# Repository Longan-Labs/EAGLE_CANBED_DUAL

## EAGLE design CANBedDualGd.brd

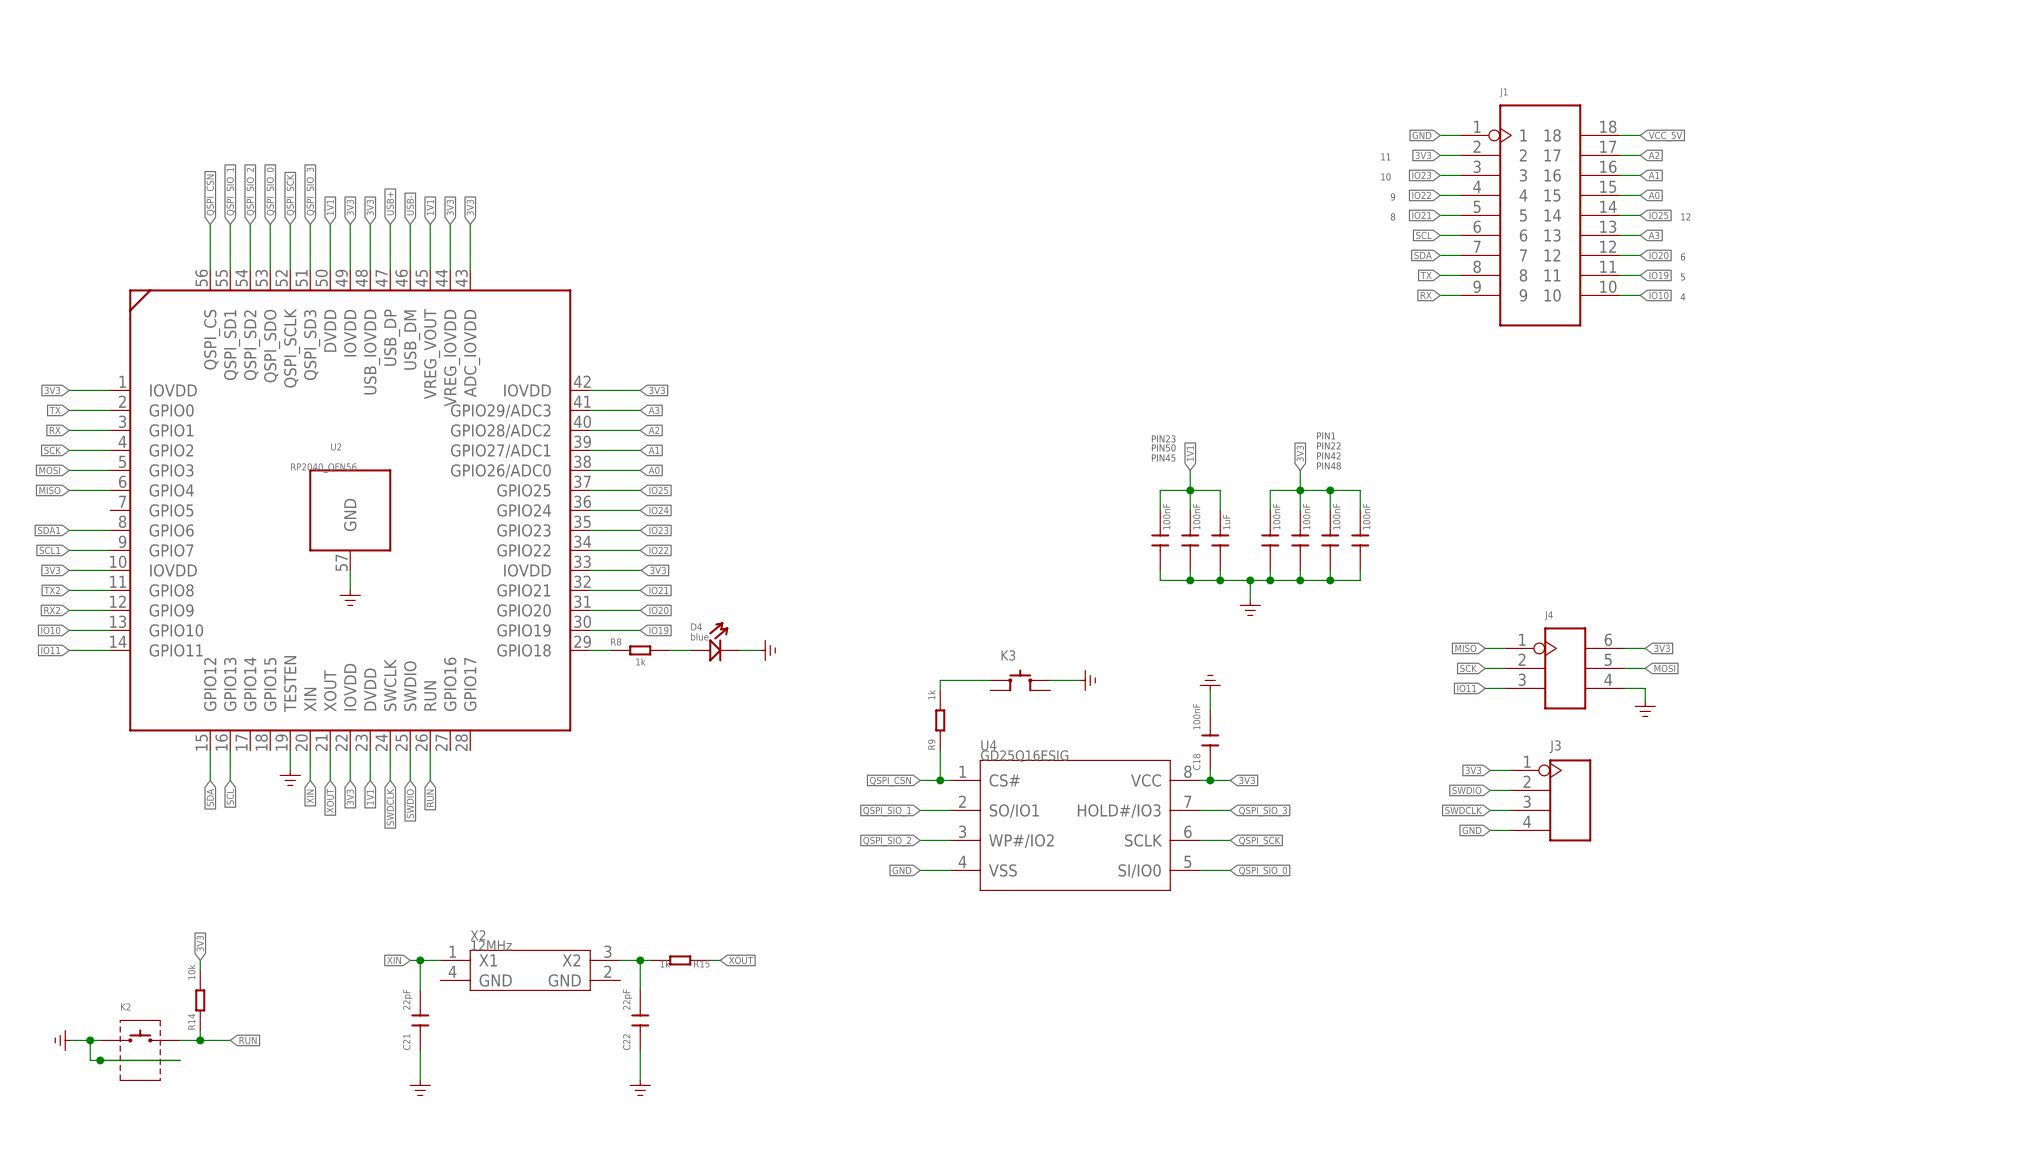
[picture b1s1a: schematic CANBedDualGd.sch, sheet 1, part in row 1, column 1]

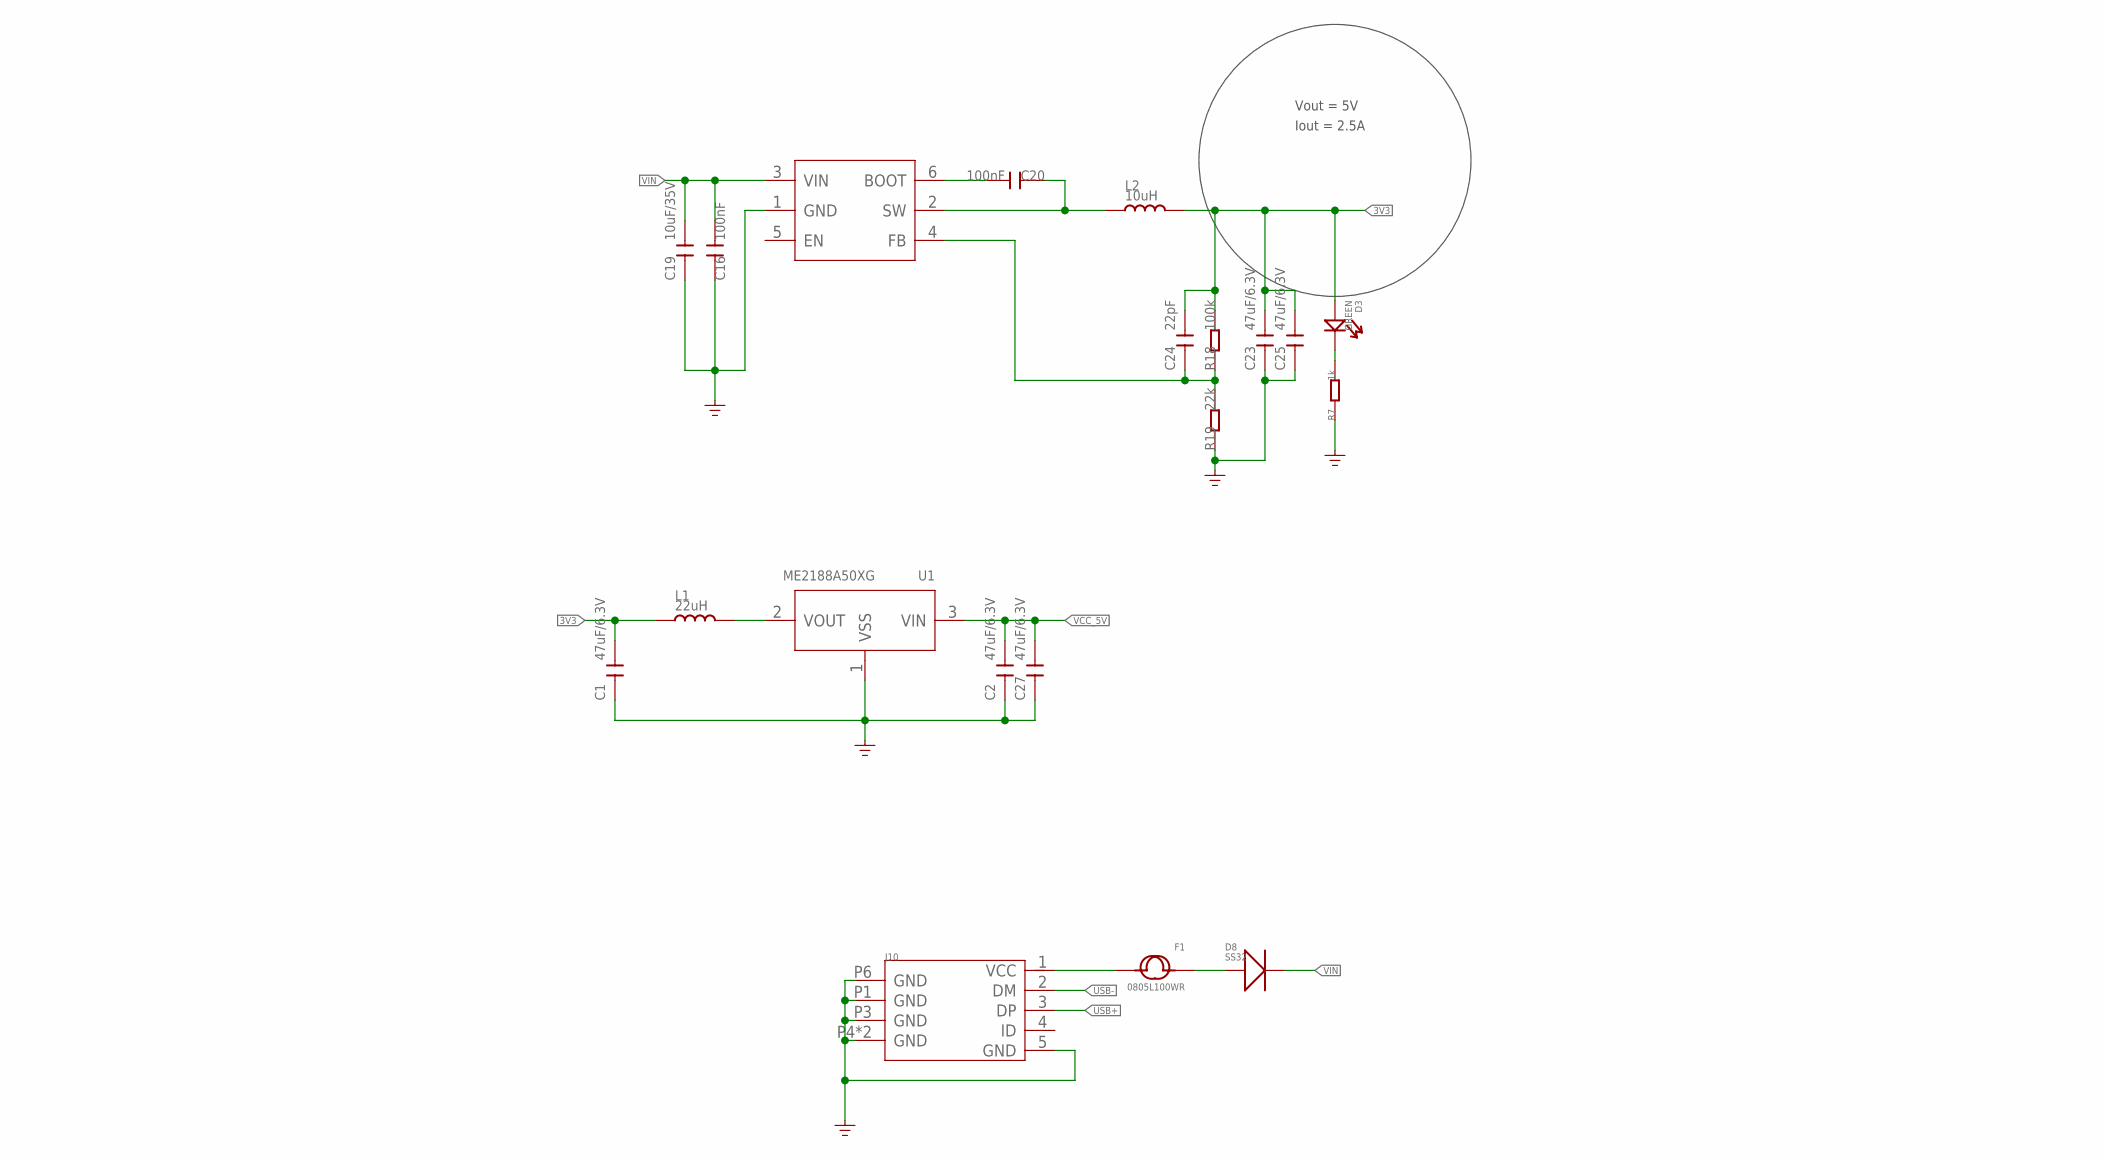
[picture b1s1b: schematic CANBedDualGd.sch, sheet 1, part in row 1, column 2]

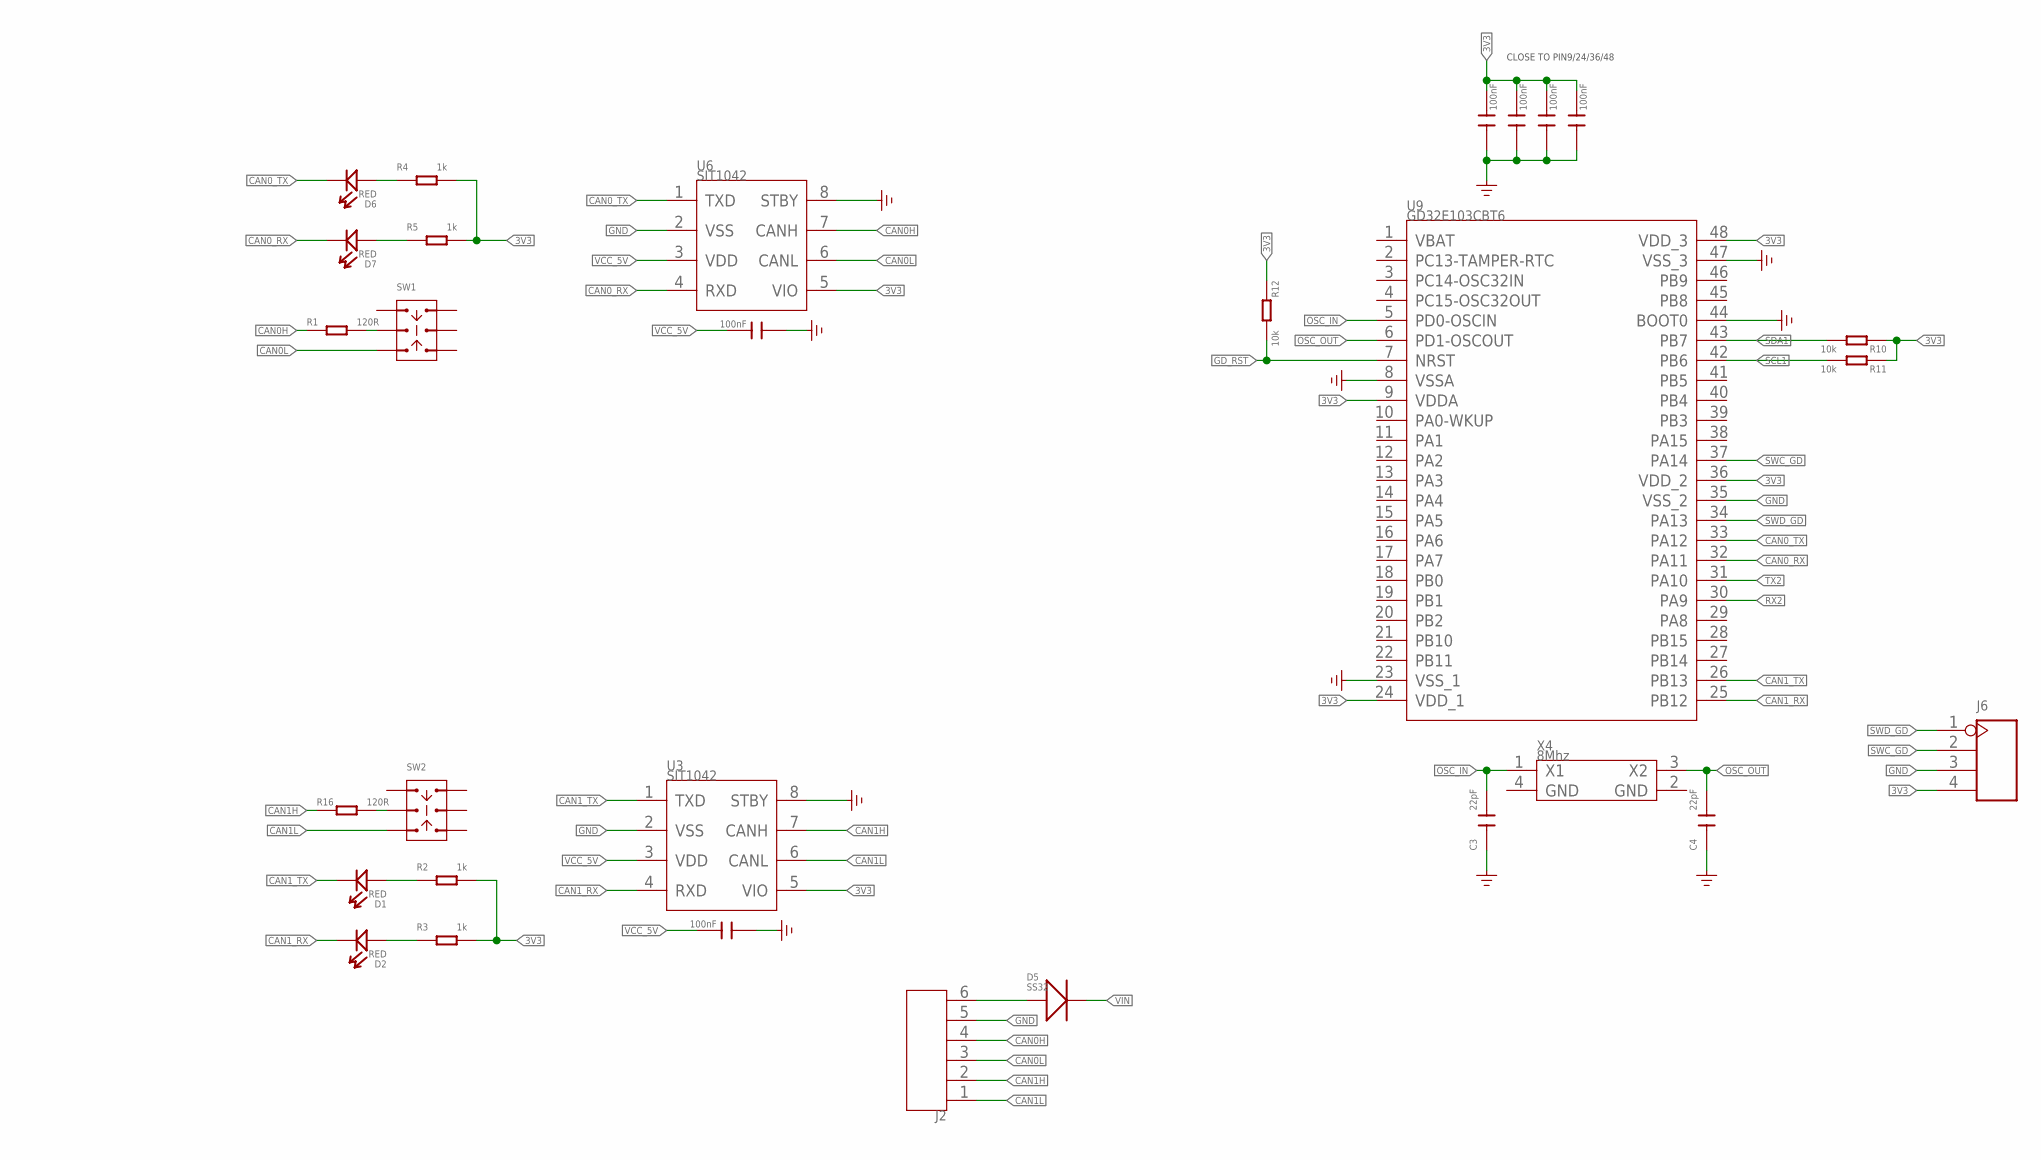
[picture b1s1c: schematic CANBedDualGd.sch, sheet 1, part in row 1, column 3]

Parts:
C1, C2, C23, C25, C27: 47uF/6.3V; C0805
C3, C4, C21, C22, C24: 22pF; C0603
C5, C6, C7, C8, C9, C10, C12, C13, C14, C15, C16, C17, C18, C20, C26: 100nF; C0603
C11: 1uF; C0603
C19: 10uF/35V; C1206
D1, D2, D6, D7: RED; LED-0603
D3: GREEN; LED-0603
D4: blue; LED-0603
D5, D8: SS32; DO-214AC
F1: 0805L100WR; F0805
J1: HEADER-2X9P-2.54; H2X9-2.54
J2: SCREW-TERMINAL-6P-3.5; H6-3.5-21.7X7.0MM
J3, J6: HEADER-4P-SMD; H4-SMD-2.54
J4: HEADER-2X3P-2.54; H2X3-2.54
J10: MICRO-USB5+4P-320010050; MICRO-USB5+5P-SMD-0.65-7.2X5.06MM
K2: BUTTON-2+2P; SW2+2P-7.7X2.75X3.95MM
K3: BUTTON-4P-4.5X4.5X3.3MM; SW4-4.5X4.5X3.3MM
L1: 22uH; L3030-TAIYO-YUDEN-NR3012
L2: 10uH; L0420
R1, R16: 120R; R0603
R2, R3, R4, R5, R7, R8, R9, R15: 1k; R0603
R10, R11, R12, R14: 10k; R0603
R18: 100k; R0603
R19: 22k; R0603
SW1, SW2: SWITCH-2CH-6P-311010004; SW6-2.54-9.0X3.5X3.2+2.0MM
U1: ME2188A50XG; SOT-23
U2: RP2040_QFN56
U3, U6: SIT1042; SOIC8-1.27-5X4MM
U4: GD25Q16ESIG; SOP8-1.27-5.3X5.25X2MM
U5: PMIC-TPS54302; SOT-23-6
U9: GD32E103CBT6; LQFP48
X2: 12MHz; X4-SMD-3.2X2.5X0.7MM
X4: 8Mhz; X4-SMD-3.2X2.5X0.7MM

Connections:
1V1: C9.2, C10.2, C11.2, U2.23 (DVDD), U2.45 (VREG_VOUT), U2.50 (DVDD)
3V3: C1.2, C5.2, C6.2, C7.2, C8.2, C12.2, C13.2, C14.2, C15.2, C18.1, C23.2, C24.2, C25.2, D3.+, J1.2, J3.1, J4.6, J6.4, L1.1, L2.2, R2.2, R3.2, R4.2, R5.2, R10.1, R11.1, R12.1, R14.2, R18.2, U2.1 (IOVDD), U2.10 (IOVDD), U2.22 (IOVDD), U2.33 (IOVDD), U2.42 (IOVDD), U2.43 (ADC_IOVDD), U2.44 (VREG_IOVDD), U2.48 (USB_IOVDD), U2.49 (IOVDD), U3.5 (VIO), U4.8 (VCC), U6.5 (VIO), U9.9 (VDDA), U9.24 (VDD_1), U9.36 (VDD_2), U9.48 (VDD_3)
A0: J1.15, U2.38 (GPIO26/ADC0)
A1: J1.16, U2.39 (GPIO27/ADC1)
A2: J1.17, U2.40 (GPIO28/ADC2)
A3: J1.13, U2.41 (GPIO29/ADC3)
CAN0H: J2.4, R1.1, U6.7 (CANH)
CAN0L: J2.3, SW1.CH1B, U6.6 (CANL)
CAN0_RX: D7.-, U6.4 (RXD), U9.32 (PA11)
CAN0_TX: D6.-, U6.1 (TXD), U9.33 (PA12)
CAN1H: J2.2, R16.1, U3.7 (CANH)
CAN1L: J2.1, SW2.CH1B, U3.6 (CANL)
CAN1_RX: D2.-, U3.4 (RXD), U9.25 (PB12)
CAN1_TX: D1.-, U3.1 (TXD), U9.26 (PB13)
EXT_PWR: F1.2, J10.1 (VCC)
GD_RST: R12.2, U9.7 (NRST)
GND: C1.1, C2.1, C3.1, C4.1, C5.1, C6.1, C7.1, C8.1, C9.1, C10.1, C11.1, C12.1, C13.1, C14.1, C15.1, C16.1, C17.1, C18.2, C19.1, C21.1, C22.1, C23.1, C25.1, C26.1, C27.1, D4.-, J1.1, J2.5, J3.4, J4.4, J6.3, J10.5 (GND), J10.P1 (GND), J10.P3 (GND), J10.P4 (GND), J10.P5 (GND), J10.P6 (GND), K2.1, K2.S1, K2.S2, K3.3 (B0), R7.1, R19.1, U1.1 (VSS), U2.19 (TESTEN), U2.57 (GND), U3.2 (VSS), U3.8 (STBY), U4.4 (VSS), U5.1 (GND), U6.2 (VSS), U6.8 (STBY), U9.8 (VSSA), U9.23 (VSS_1), U9.35 (VSS_2), U9.44 (BOOT0), U9.47 (VSS_3)
IO10: J1.10, U2.13 (GPIO10)
IO11: J4.3, U2.14 (GPIO11)
IO19: J1.11, U2.30 (GPIO19)
IO20: J1.12, U2.31 (GPIO20)
IO21: J1.5, U2.32 (GPIO21)
IO22: J1.4, U2.34 (GPIO22)
IO23: J1.3, U2.35 (GPIO23)
IO24: U2.36 (GPIO24)
IO25: J1.14, U2.37 (GPIO25)
MISO: J4.1, U2.6 (GPIO4)
MOSI: J4.5, U2.5 (GPIO3)
unnamed: D3.-, R7.2
unnamed: D1.+, R2.1
unnamed: R8.1, U2.29 (GPIO18)
unnamed: R1.2, SW1.COM1
unnamed: R16.2, SW2.COM1
unnamed: D4.+, R8.2
unnamed: K3.1 (A0), R9.2
unnamed: C22.2, R15.2, X2.3 (X2)
unnamed: D6.+, R4.1
unnamed: D7.+, R5.1
unnamed: D8.1 (+), F1.1
unnamed: C20.1, L2.1, U5.2 (SW)
unnamed: C20.2, U5.6 (BOOT)
unnamed: D2.+, R3.1
unnamed: L1.2, U1.2 (VOUT)
unnamed: D5.1 (+), J2.6
unnamed: C24.1, R18.1, R19.2, U5.4 (FB)
OSC_IN: C3.2, U9.5 (PD0-OSCIN), X4.1 (X1)
OSC_OUT: C4.2, U9.6 (PD1-OSCOUT), X4.3 (X2)
QSPI_CSN: R9.1, U2.56 (QSPI_CS), U4.1 (CS#)
QSPI_SCK: U2.52 (QSPI_SCLK), U4.6 (SCLK)
QSPI_SIO_0: U2.53 (QSPI_SDO), U4.5 (SI/IO0)
QSPI_SIO_1: U2.55 (QSPI_SD1), U4.2 (SO/IO1)
QSPI_SIO_2: U2.54 (QSPI_SD2), U4.3 (WP#/IO2)
QSPI_SIO_3: U2.51 (QSPI_SD3), U4.7 (HOLD#/IO3)
RUN: K2.2, R14.1, U2.26 (RUN)
RX: J1.9, U2.3 (GPIO1)
RX2: U2.12 (GPIO9), U9.30 (PA9)
SCK: J4.2, U2.4 (GPIO2)
SCL: J1.6, U2.16 (GPIO13)
SCL1: R11.2, U2.9 (GPIO7), U9.42 (PB6)
SDA: J1.7, U2.15 (GPIO12)
SDA1: R10.2, U2.8 (GPIO6), U9.43 (PB7)
SWC_GD: J6.2, U9.37 (PA14)
SWDCLK: J3.3, U2.24 (SWCLK)
SWDIO: J3.2, U2.25 (SWDIO)
SWD_GD: J6.1, U9.34 (PA13)
TX: J1.8, U2.2 (GPIO0)
TX2: U2.11 (GPIO8), U9.31 (PA10)
USB+: J10.3 (DP), U2.47 (USB_DP)
USB-: J10.2 (DM), U2.46 (USB_DM)
VCC_5V: C2.2, C17.2, C26.2, C27.2, J1.18, U1.3 (VIN), U3.3 (VDD), U6.3 (VDD)
VIN: C16.2, C19.2, D5.2 (-), D8.2 (-), U5.3 (VIN)
XIN: C21.2, U2.20 (XIN), X2.1 (X1)
XOUT: R15.1, U2.21 (XOUT)

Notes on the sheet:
PIN1
PIN22
PIN42
PIN48
PIN23
PIN50
PIN45
CLOSE TO PIN9/24/36/48
Vout = 5V
Iout = 2.5A

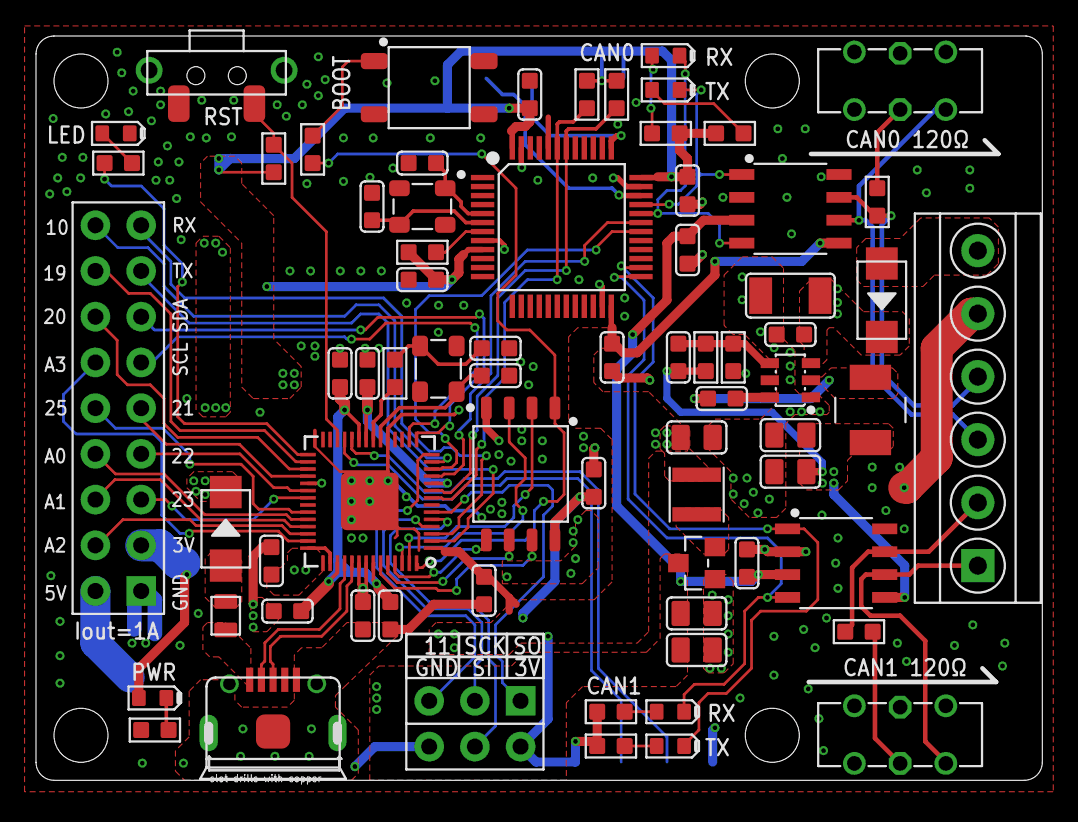
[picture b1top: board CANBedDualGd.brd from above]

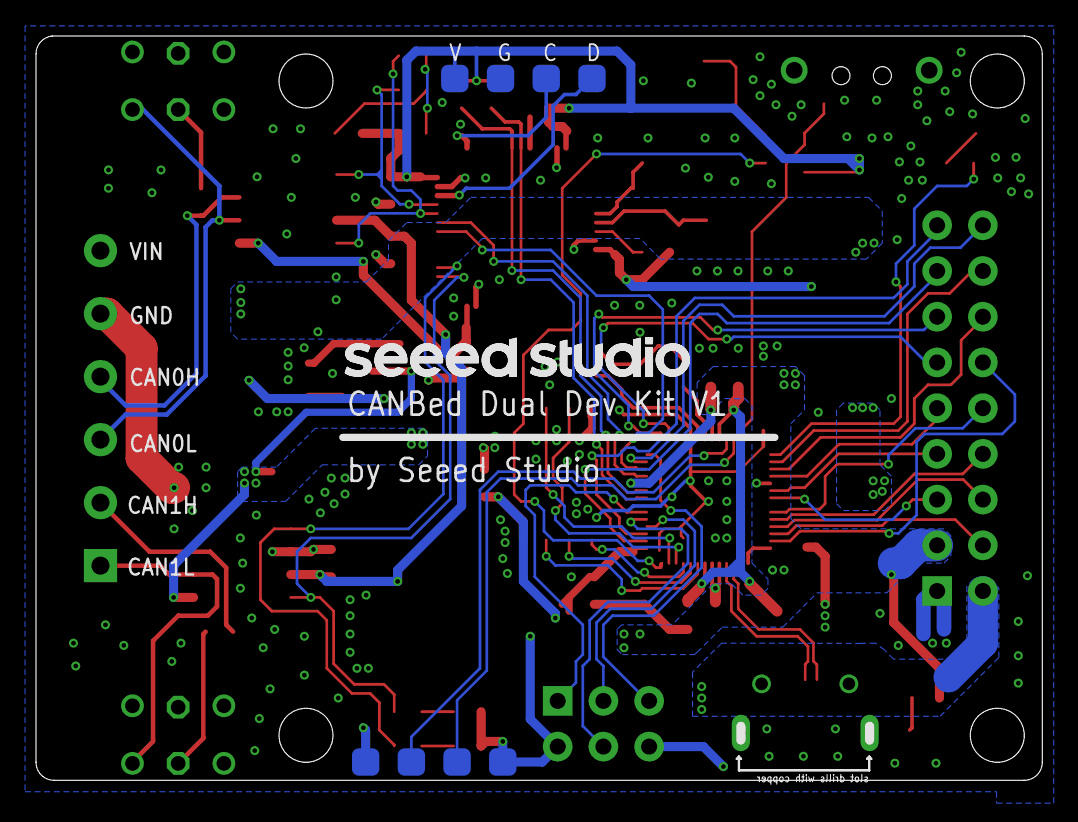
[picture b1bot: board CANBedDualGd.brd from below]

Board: 2 copper layers, 55.4 x 41.2 mm, 74 parts (3 on the bottom side), 72 nets.

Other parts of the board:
U$23: LOGO-SEEED-NEW-2_1X19.1MM
